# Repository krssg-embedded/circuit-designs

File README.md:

# Circuit Design
This repo contains all the schematics and pcb layout designs relevant to the SSL bot.
There are three imporatant circuits in the bot:
1. Main Board
2. Kicker Circuit
3. Motor Driver

### Main Board

### Kicker Circuit
The kicker we use works on the principle of a solenoid.
The straight kicker is powered by two 250V 2200uF capacitors, which can be charged by a step-up converter to 200V each.
The kicker board constitutes of a charging and a discharging circuit. The FPGA on the main circuit is controlling the circuit. The board receives charge trigger and kicking level from the main circuit, charging the capacitor bank of 4400uF to 250V using flyback topology.
The charging circuit is based on LT3750, a flyback converter. It consists of a different resistor which can be used to change various output parameters like charging current. The CHARGE pin one the IC gives full control of the LT3750 to the user and the DONE pin indicates when the capacitor has reached its programmed value, and the part has stopped charging.
The capacitor is charged to its limit by using a boost convertor that steps up the voltage from the the 12V battery. The kicker is operated through a switch which disconnects the charging circuit and allows the charge from the capacitor to flow through the solenoid. 
As the kicker is made of a magnetic material as soon as the current flows the coil tries to bring as much of the kicker inside itself as possible. This is what generates the tremendous kicking force required to kick the ball.

### Motor Driver
MOTOR DRIVER
In motor driver, I learnt how to make a commutation table.
I learnt in detail about the internal circuitry of the driver. I read about power MOSFETs and their advantages. We were taught the problems that we currently face in running our BLDCs. I learnt to place the components on the PCB and solder them properly. I also read about the gate driver IC we use and how it helps us in switching the states of the mosfets.
I read about the various methods of sensing commutation which includes using Hall sensors, using encoders and finally back-EMF calculations. The methods of control like trapezoidal, sinusoidal and field oriented control. The current sensor IC ACS2590 was also introduced. 
The main takeaway was that there are problems in the circuitry that we use and many things can be improved like we can implement sinusoidal current by applying variable PWM or make the commutation smoother by adjusting the rise and fall time of the voltages at the gates.

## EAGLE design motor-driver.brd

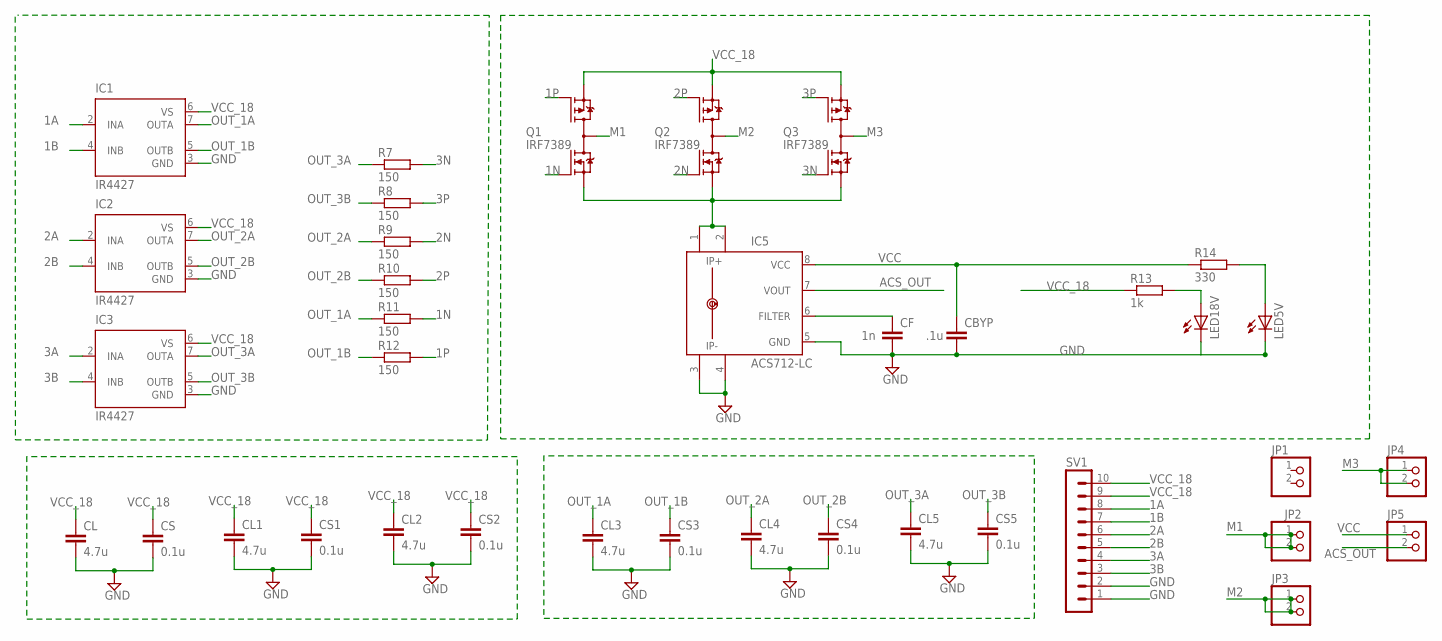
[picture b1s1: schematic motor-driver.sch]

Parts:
CBYP: .1u; C1206
CF: 1n; C1206
CL, CL1, CL2, CL3, CL4, CL5: 4.7u; C1206
CS, CS1, CS2, CS3, CS4, CS5: 0.1u; C1206
IC1, IC2, IC3: IR4427; DIL08
IC5: ACS712-LC; SOIC8
JP1, JP2, JP3, JP4, JP5: PINHD-1X2; 1X02
LED5V, LED18V: LEDCHIPLED_1206; CHIPLED_1206
Q1, Q2, Q3: IRF7389; SO08-IRF
R7, R8, R9, R10, R11, R12: 150; R1206
R13: 1k; R1206
R14: 330; R1206
SV1: MA10-1

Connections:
1A: IC1.2 (INA), SV1.8
1B: IC1.4 (INB), SV1.7
1N: Q1.2 (N-G), R11.2
1P: Q1.4 (P-G), R12.2
2A: IC2.2 (INA), SV1.6
2B: IC2.4 (INB), SV1.5
2N: Q2.2 (N-G), R9.2
2P: Q2.4 (P-G), R10.2
3A: IC3.2 (INA), SV1.4
3B: IC3.4 (INB), SV1.3
3N: Q3.2 (N-G), R7.2
3P: Q3.4 (P-G), R8.2
ACS_OUT: IC5.7 (VOUT), JP5.2
FILTER_ACS: CF.1, IC5.6 (FILTER)
GND: CBYP.2, CF.2, CL.2, CL1.2, CL2.2, CL3.2, CL4.2, CL5.2, CS.2, CS1.2, CS2.2, CS3.2, CS4.2, CS5.2, IC1.3 (GND), IC2.3 (GND), IC3.3 (GND), IC5.3 (IP-), IC5.4 (IP-1), IC5.5 (GND), LED5V.C, LED18V.C, SV1.1, SV1.2
M1: JP2.1, JP2.2, Q1.5 (D), Q1.6 (D), Q1.7 (D), Q1.8 (D)
M2: JP3.1, JP3.2, Q2.5 (D), Q2.6 (D), Q2.7 (D), Q2.8 (D)
M3: JP4.1, JP4.2, Q3.5 (D), Q3.6 (D), Q3.7 (D), Q3.8 (D)
unnamed: LED18V.A, R13.2
unnamed: LED5V.A, R14.2
OUT_1A: CL3.1, IC1.7 (OUTA), R11.1
OUT_1B: CS3.1, IC1.5 (OUTB), R12.1
OUT_2A: CL4.1, IC2.7 (OUTA), R9.1
OUT_2B: CS4.1, IC2.5 (OUTB), R10.1
OUT_3A: CL5.1, IC3.7 (OUTA), R7.1
OUT_3B: CS5.1, IC3.5 (OUTB), R8.1
SINK: IC5.1 (IP+), IC5.2 (IP+1), Q1.1 (N-S), Q2.1 (N-S), Q3.1 (N-S)
VCC: CBYP.1, IC5.8 (VCC), JP5.1, R14.1
VCC_18: CL.1, CL1.1, CL2.1, CS.1, CS1.1, CS2.1, IC1.6 (VS), IC2.6 (VS), IC3.6 (VS), Q1.3 (P-S), Q2.3 (P-S), Q3.3 (P-S), R13.1, SV1.9, SV1.10

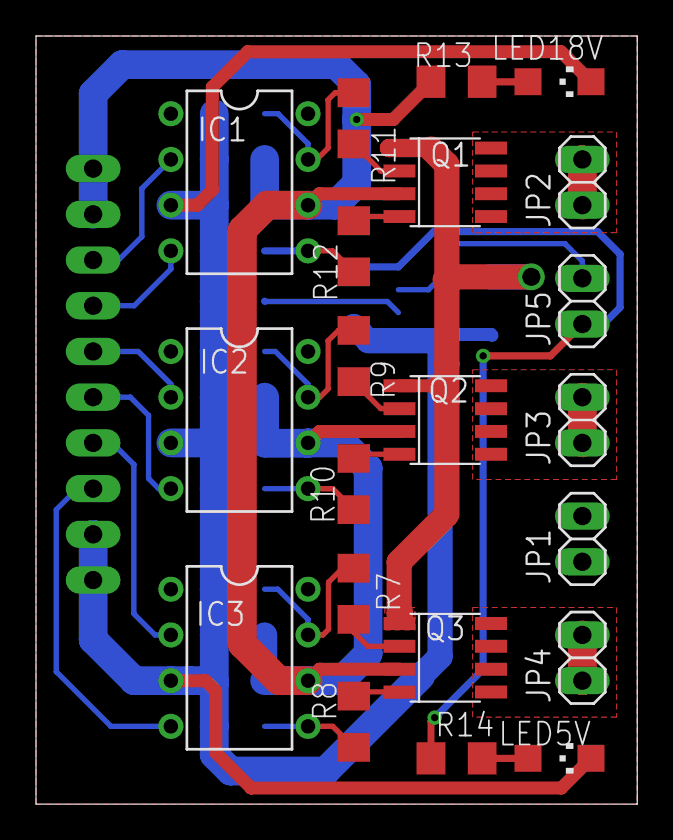
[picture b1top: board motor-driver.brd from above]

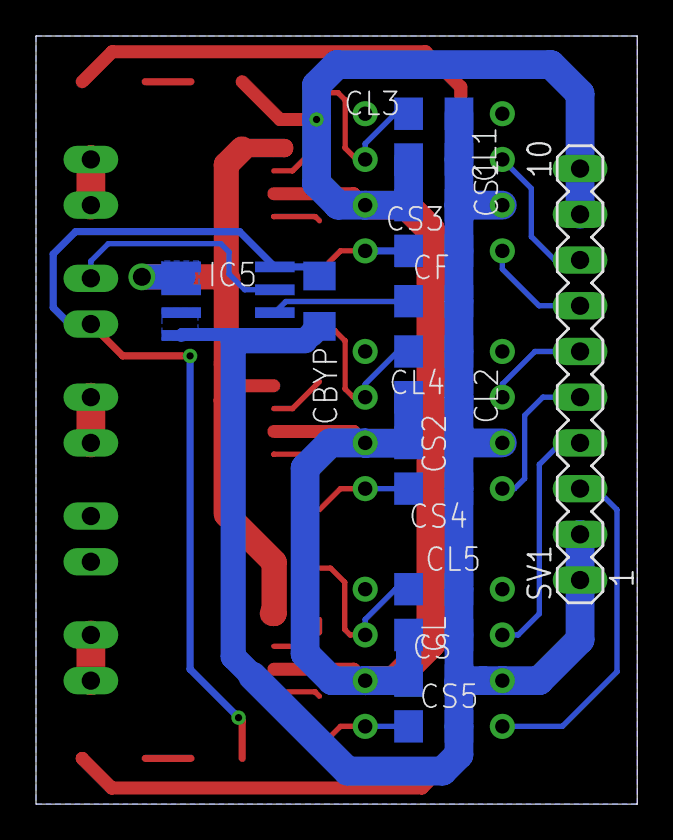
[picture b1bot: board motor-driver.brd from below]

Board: 2 copper layers, 33.4 x 42.7 mm, 37 parts (16 on the bottom side), 29 nets.

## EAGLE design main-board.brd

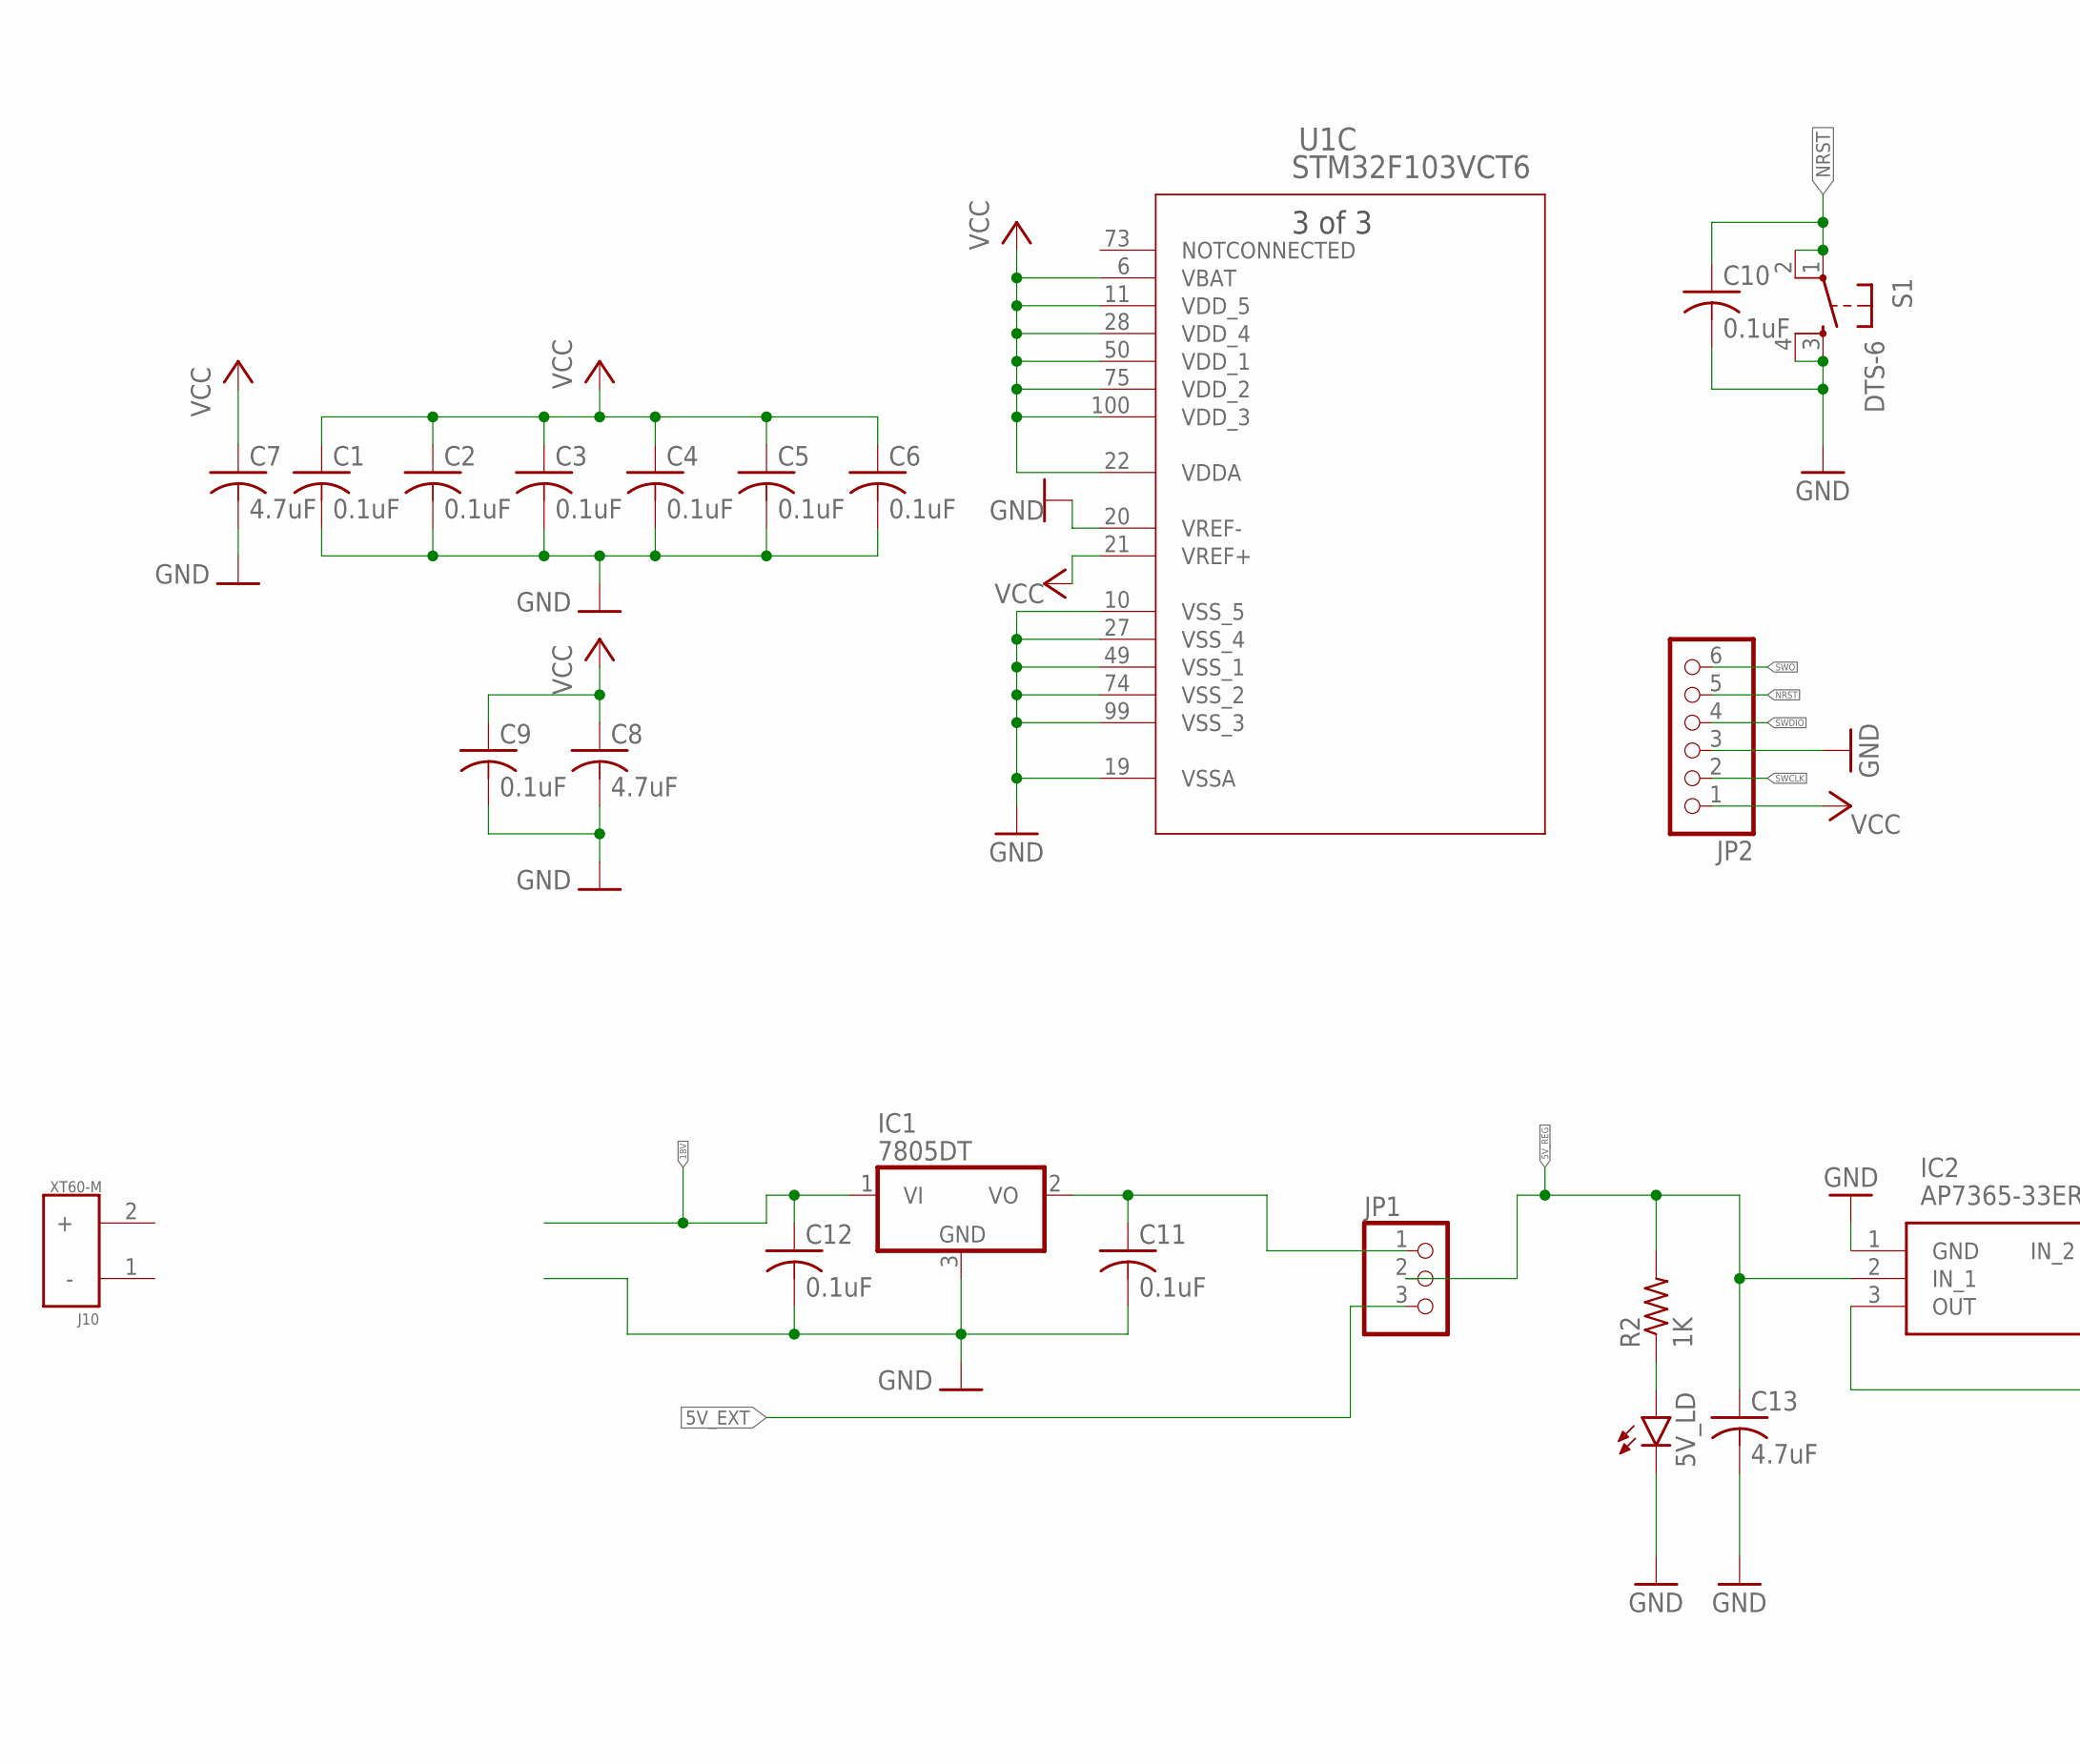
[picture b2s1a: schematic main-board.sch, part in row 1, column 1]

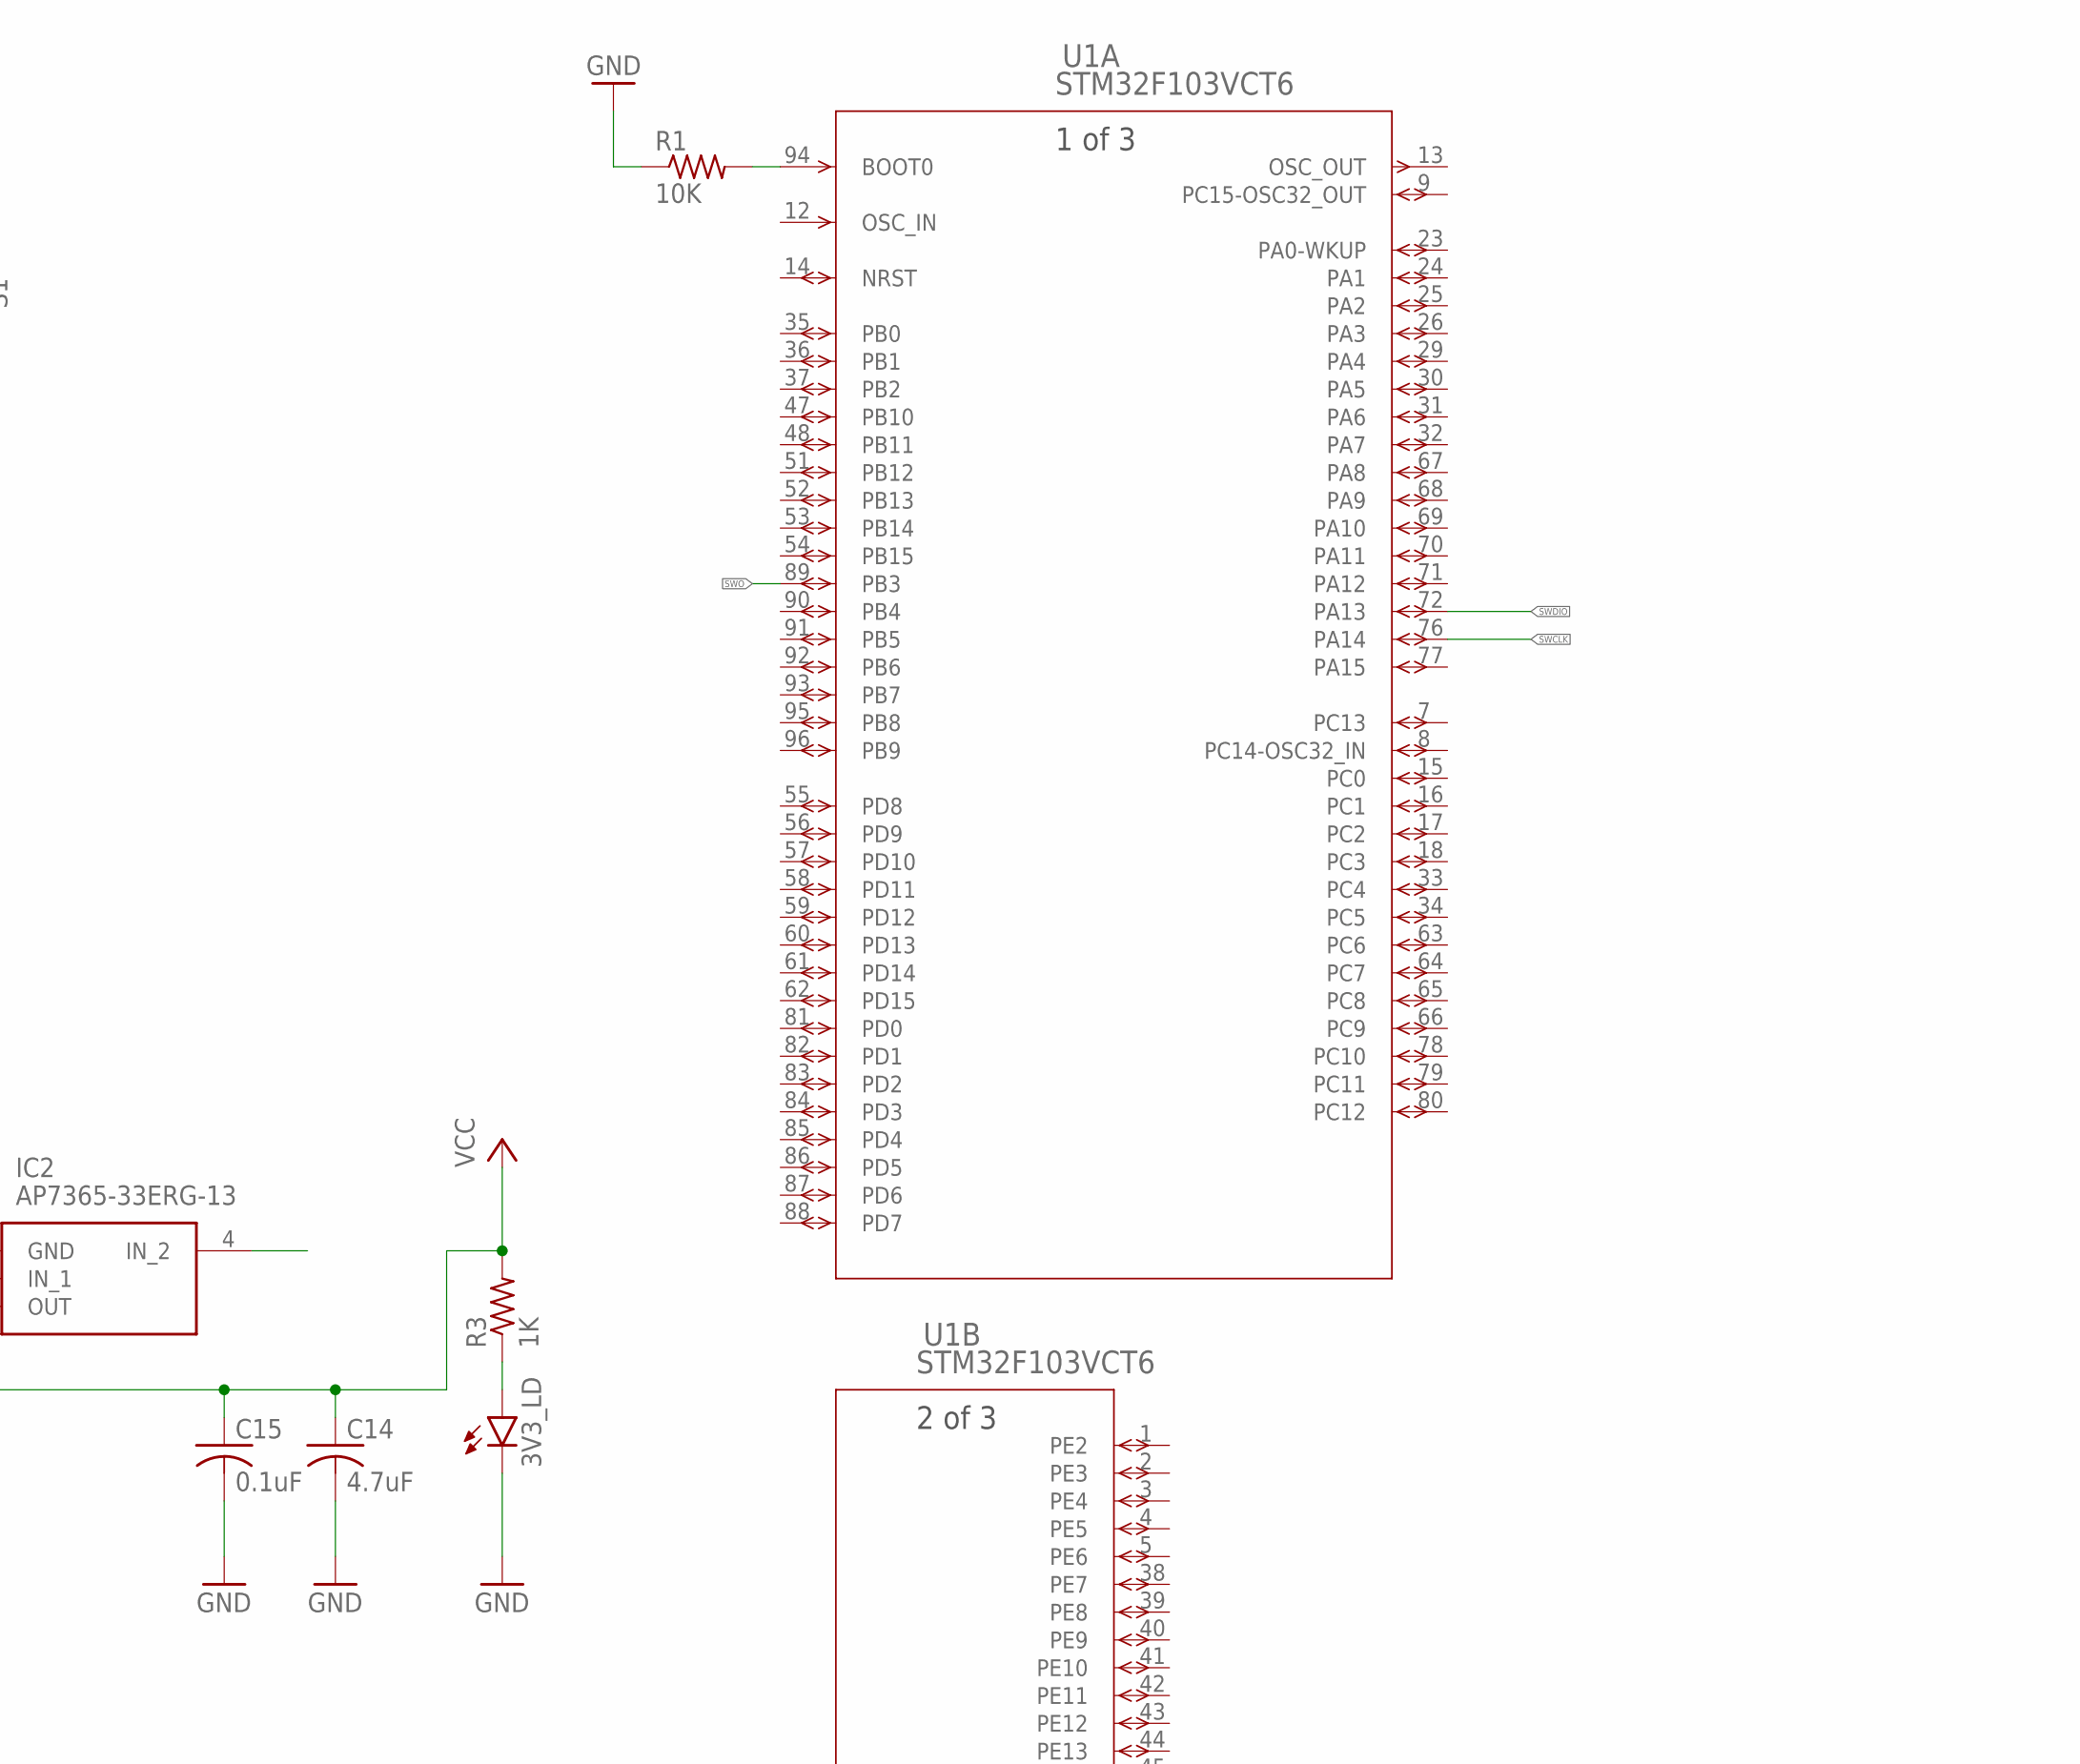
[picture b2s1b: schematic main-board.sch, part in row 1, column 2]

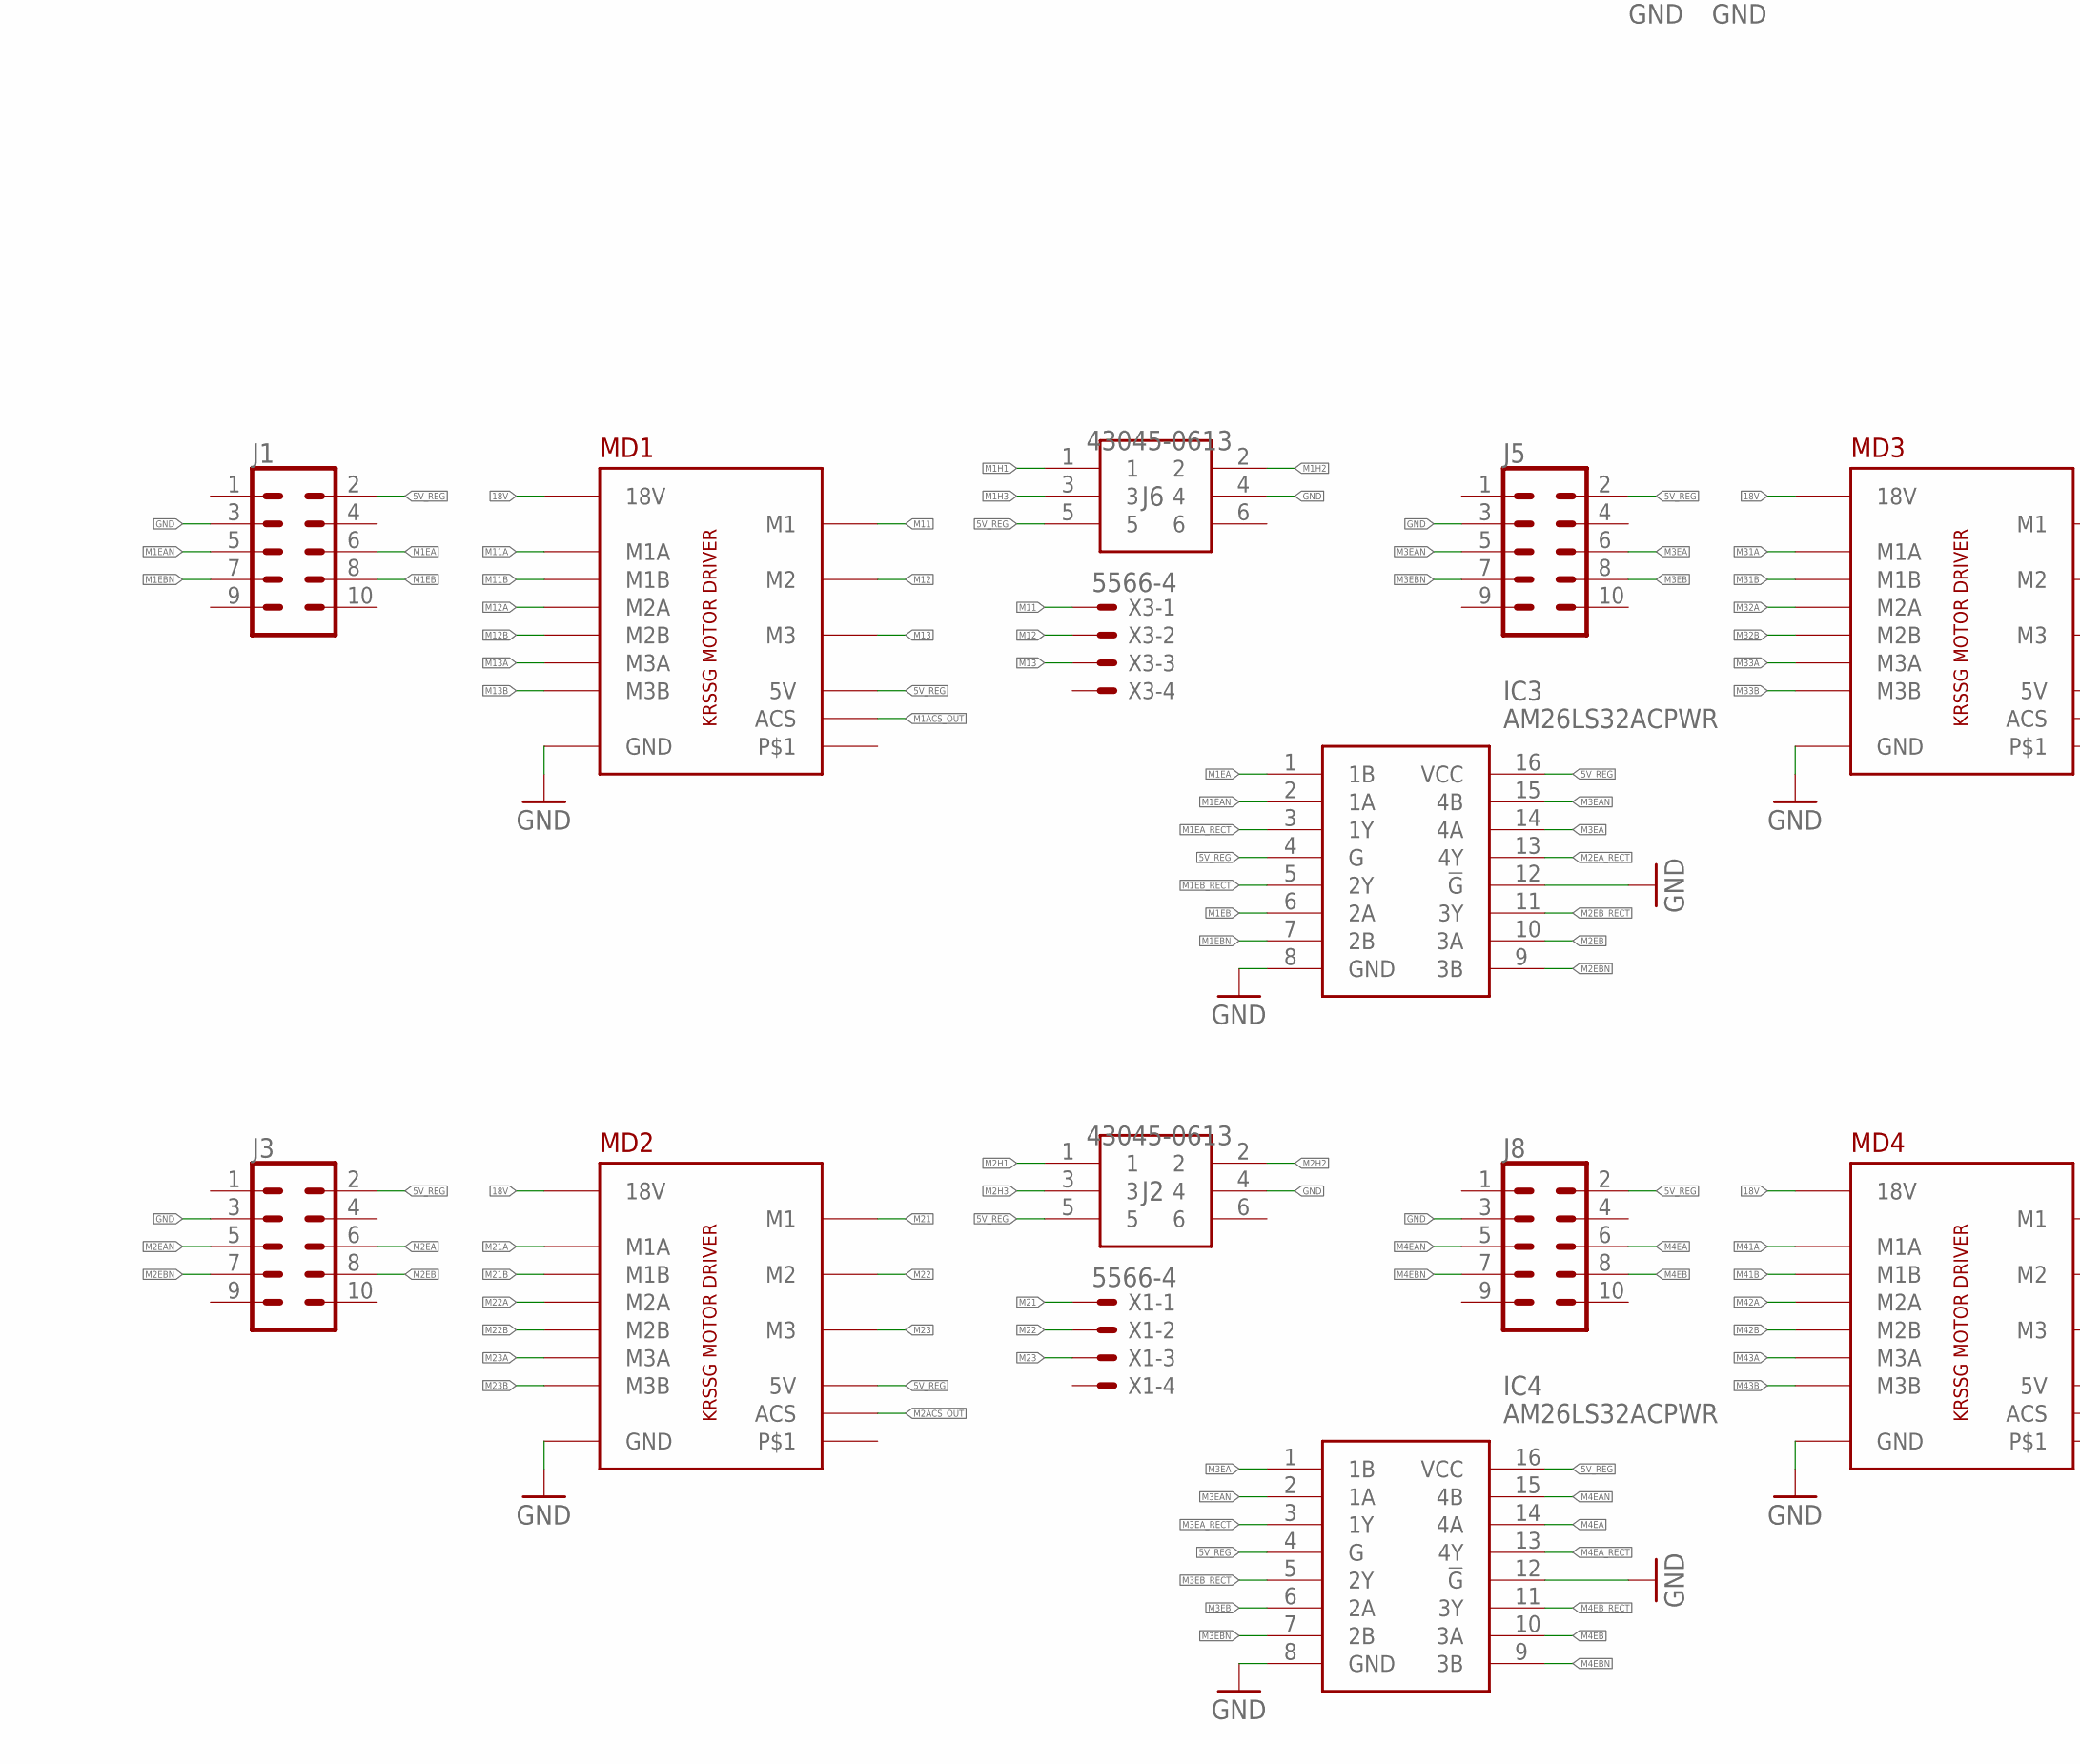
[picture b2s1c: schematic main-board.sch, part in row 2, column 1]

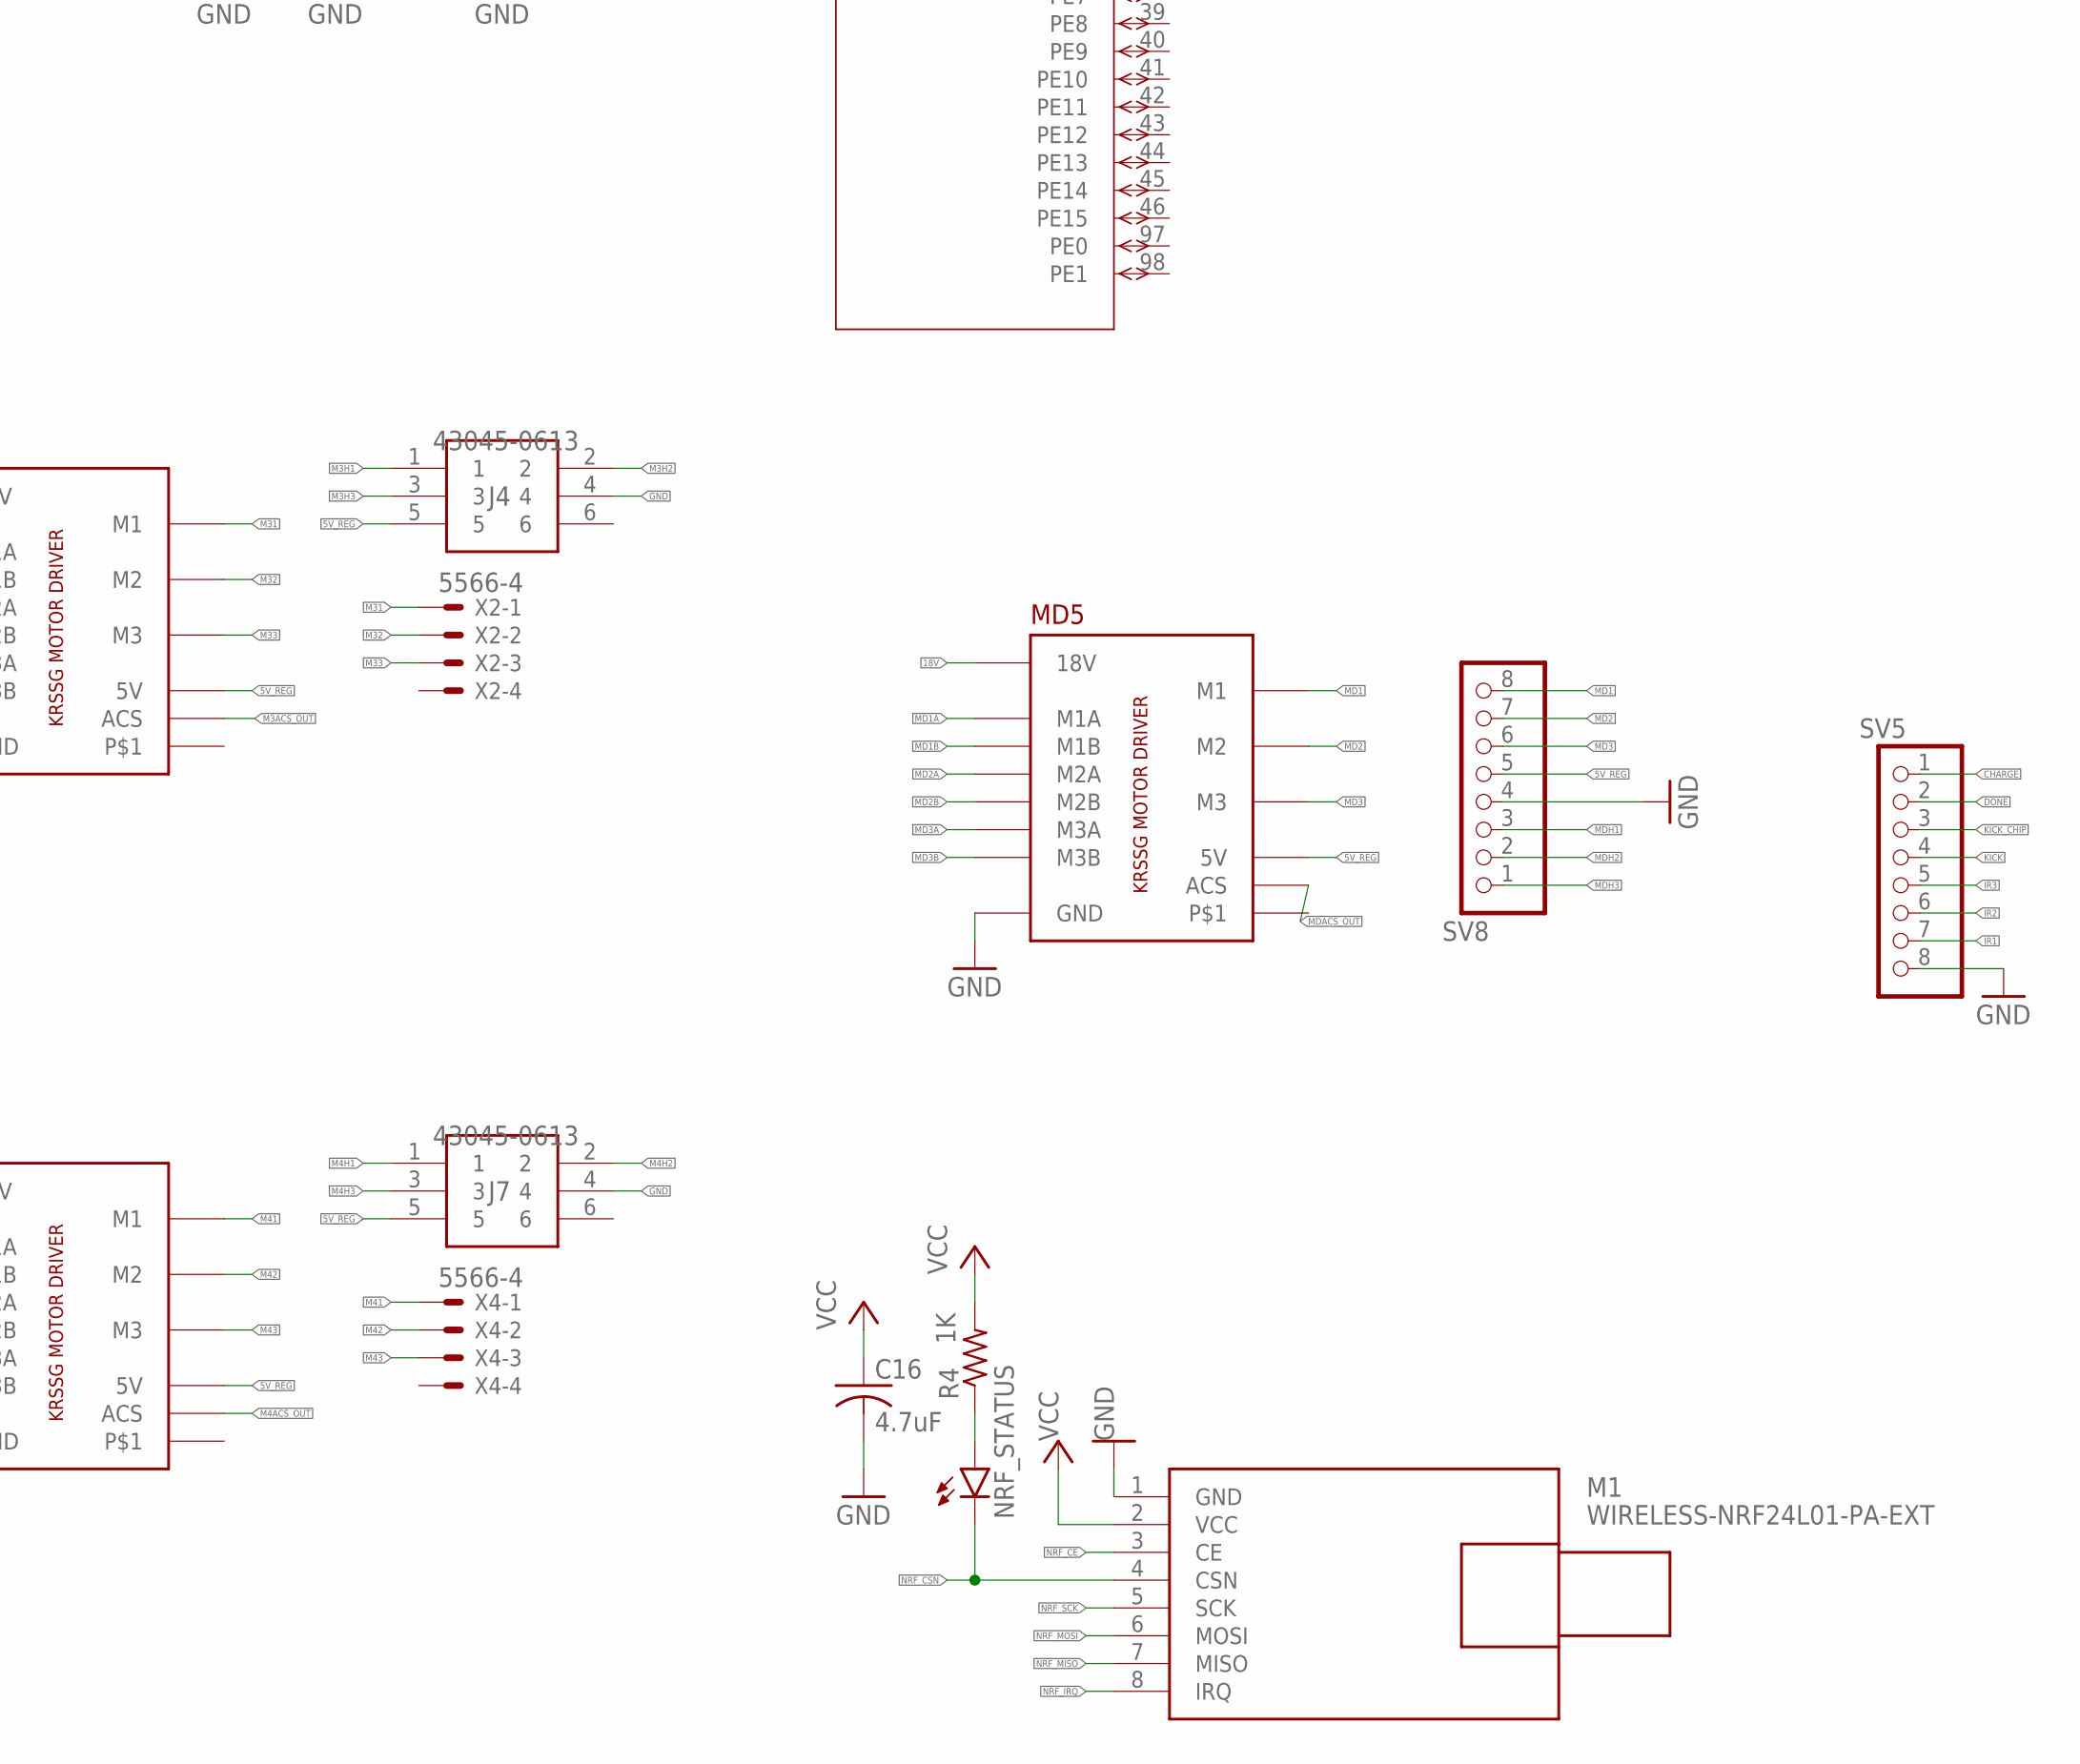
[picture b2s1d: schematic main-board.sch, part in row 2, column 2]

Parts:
3V3_LD, 5V_LD: LEDCHIPLED_1206; CHIPLED_1206
C1, C2, C3, C4, C5, C6, C9, C10, C11, C12, C15: 0.1uF; C1206
C7, C8, C13, C14, C16: 4.7uF; C1206
IC1: 7805DT; TO252
IC2: AP7365-33ERG-13; SOT230P700X180-4N
IC3, IC4: AM26LS32ACPWR; SOP65P640X120-16N
J1, J3, J5, J8: CONN_05X2SHD_LOCK; 2X5-SHROUDED_LOCK
J2, J4, J6, J7: 43045-0613
J10: XT60-M; AMASS_XT60-M
JP1: PINHD-1X3; 1X03
JP2: PINHD-1X6; 1X06
M1: WIRELESS-NRF24L01-PA-EXT; WIRELESS-NRD24L01-PA-EXT
MD1, MD2, MD3, MD4, MD5: KRSSG_MOTOR_DRIVER
NRF_STATUS: LEDCHIPLED_1206; CHIPLED_1206
R1: 10K; M1206
R2, R3, R4: 1K; M1206
S1: DTS-6
SV5, SV8: PINHD-1X8; 1X08
U1: STM32F103VCT6; LQFP100-14X14MM
X1, X2, X3, X4: 5566-4

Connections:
5V_EXT: JP1.3
5V_REG: C13.1, IC2.2 (IN_1), IC2.4 (IN_2), IC3.4 (G), IC3.16 (VCC), IC4.4 (G), IC4.16 (VCC), J1.2, J2.5, J3.2, J4.5, J5.2, J6.5, J7.5, J8.2, JP1.2, MD1.5V, MD2.5V, MD3.5V, MD4.5V, MD5.5V, R2.2, SV8.5
18V: C12.1, IC1.1 (VI), MD1.18V, MD1.18V_2 (18V), MD2.18V, MD2.18V_2 (18V), MD3.18V, MD3.18V_2 (18V), MD4.18V, MD4.18V_2 (18V), MD5.18V, MD5.18V_2 (18V)
CHARGE: SV5.1
DONE: SV5.2
GND: 3V3_LD.C, 5V_LD.C, C1.2, C2.2, C3.2, C4.2, C5.2, C6.2, C7.2, C8.2, C9.2, C10.2, C11.2, C12.2, C13.2, C14.2, C15.2, C16.2, IC1.3 (GND), IC2.1 (GND), IC3.8 (GND), IC3.12 (!G), IC4.8 (GND), IC4.12 (!G), J1.3, J2.4, J3.3, J4.4, J5.3, J6.4, J7.4, J8.3, JP2.3, M1.1 (GND), MD1.GND, MD1.GND_2 (GND), MD2.GND, MD2.GND_2 (GND), MD3.GND, MD3.GND_2 (GND), MD4.GND, MD4.GND_2 (GND), MD5.GND, MD5.GND_2 (GND), R1.1, S1.3, S1.4, SV5.8, SV8.4, U1.10 (VSS_5), U1.19 (VSSA), U1.20 (VREF-), U1.27 (VSS_4), U1.49 (VSS_1), U1.74 (VSS_2), U1.99 (VSS_3)
IR1: SV5.7
IR2: SV5.6
IR3: SV5.5
KICK: SV5.4
KICK_CHIP: SV5.3
M1ACS_OUT: MD1.MACS_OUT (ACS)
M1EA: IC3.1 (1B), J1.6
M1EAN: IC3.2 (1A), J1.5
M1EA_RECT: IC3.3 (1Y)
M1EB: IC3.6 (2A), J1.8
M1EBN: IC3.7 (2B), J1.7
M1EB_RECT: IC3.5 (2Y)
M1H1: J6.1
M1H2: J6.2
M1H3: J6.3
M2ACS_OUT: MD2.MACS_OUT (ACS)
M2EA: J3.6
M2EAN: J3.5
M2EA_RECT: IC3.13 (4Y)
M2EB: IC3.10 (3A), J3.8
M2EBN: IC3.9 (3B), J3.7
M2EB_RECT: IC3.11 (3Y)
M2H1: J2.1
M2H2: J2.2
M2H3: J2.3
M3ACS_OUT: MD3.MACS_OUT (ACS)
M3EA: IC3.14 (4A), IC4.1 (1B), J5.6
M3EAN: IC3.15 (4B), IC4.2 (1A), J5.5
M3EA_RECT: IC4.3 (1Y)
M3EB: IC4.6 (2A), J5.8
M3EBN: IC4.7 (2B), J5.7
M3EB_RECT: IC4.5 (2Y)
M3H1: J4.1
M3H2: J4.2
M3H3: J4.3
M4ACS_OUT: MD4.MACS_OUT (ACS)
M4EA: IC4.14 (4A), J8.6
M4EAN: IC4.15 (4B), J8.5
M4EA_RECT: IC4.13 (4Y)
M4EB: IC4.10 (3A), J8.8
M4EBN: IC4.9 (3B), J8.7
M4EB_RECT: IC4.11 (3Y)
M4H1: J7.1
M4H2: J7.2
M4H3: J7.3
M11: MD1.M1, MD1.M1_2 (M1), X3.1
M11A: MD1.M1A
M11B: MD1.M1B
M12: MD1.M2, MD1.M2_2 (M2), X3.2
M12A: MD1.M2A
M12B: MD1.M2B
M13: MD1.M3, MD1.M3_2 (M3), X3.3
M13A: MD1.M3A
M13B: MD1.M3B
M21: MD2.M1, MD2.M1_2 (M1), X1.1
M21A: MD2.M1A
M21B: MD2.M1B
M22: MD2.M2, MD2.M2_2 (M2), X1.2
M22A: MD2.M2A
M22B: MD2.M2B
M23: MD2.M3, MD2.M3_2 (M3), X1.3
M23A: MD2.M3A
M23B: MD2.M3B
M31: MD3.M1, MD3.M1_2 (M1), X2.1
M31A: MD3.M1A
M31B: MD3.M1B
M32: MD3.M2, MD3.M2_2 (M2), X2.2
M32A: MD3.M2A
M32B: MD3.M2B
M33: MD3.M3, MD3.M3_2 (M3), X2.3
M33A: MD3.M3A
M33B: MD3.M3B
M41: MD4.M1, MD4.M1_2 (M1), X4.1
M41A: MD4.M1A
M41B: MD4.M1B
M42: MD4.M2, MD4.M2_2 (M2), X4.2
M42A: MD4.M2A
M42B: MD4.M2B
M43: MD4.M3, MD4.M3_2 (M3), X4.3
M43A: MD4.M3A
M43B: MD4.M3B
MD1: MD5.M1, MD5.M1_2 (M1), SV8.8
MD1A: MD5.M1A
MD1B: MD5.M1B
MD2: MD5.M2, MD5.M2_2 (M2), SV8.7
MD2A: MD5.M2A
MD2B: MD5.M2B
MD3: MD5.M3, MD5.M3_2 (M3), SV8.6
MD3A: MD5.M3A
MD3B: MD5.M3B
MDACS_OUT: MD5.MACS_OUT (ACS)
MDH1: SV8.3
MDH2: SV8.2
MDH3: SV8.1
unnamed: R1.2, U1.94 (BOOT0)
unnamed: 3V3_LD.A, R3.1
unnamed: C11.1, IC1.2 (VO), JP1.1
unnamed: 5V_LD.A, R2.1
unnamed: NRF_STATUS.A, R4.1
NRF_CE: M1.3 (CE)
NRF_CSN: M1.4 (CSN), NRF_STATUS.C
NRF_IRQ: M1.8 (IRQ)
NRF_MISO: M1.7 (MISO)
NRF_MOSI: M1.6 (MOSI)
NRF_SCK: M1.5 (SCK)
NRST: C10.1, JP2.5, S1.1, S1.2
SWCLK: JP2.2, U1.76 (PA14)
SWDIO: JP2.4, U1.72 (PA13)
SWO: JP2.6, U1.89 (PB3)
VCC: C1.1, C2.1, C3.1, C4.1, C5.1, C6.1, C7.1, C8.1, C9.1, C14.1, C15.1, C16.1, IC2.3 (OUT), JP2.1, M1.2 (VCC), R3.2, R4.2, U1.6 (VBAT), U1.11 (VDD_5), U1.21 (VREF+), U1.22 (VDDA), U1.28 (VDD_4), U1.50 (VDD_1), U1.75 (VDD_2), U1.100 (VDD_3)

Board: 2 copper layers, 53 parts (0 on the bottom side), 43 nets, no tracks yet.

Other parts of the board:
U$1: LOGO3

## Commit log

2022-07-26 designed v2 of main board
2022-07-26 changed names
2022-07-26 removed redundant files
2022-10-15 applied some finishing touch
2023-02-26 changed file structure

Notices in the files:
parts and their libraries:
SparkFun-Connectors: Licensing: Creative Commons ShareAlike 4.0 International - https://creativecommons.org/licenses/by-sa/4.0
diy_modules_2: Released under the Creative Commons Attribution 4.0 International License: http://creativecommons.org/licenses/by/4.0
